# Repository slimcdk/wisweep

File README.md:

Feel free to support me and the development I do!

# WiSweep

Compact WiFi and Bluetooth (5.0) / ZigBee NEMA17 stepper controller featuring stall detection and ultra silent operation. Supply 5-36V upto 3A.

## Production files

## Contribution

Clone repository and fetch submodules

```bash
$ git clone --recursive-submodules git@github.com:slimcdk/wisweep.git
```

## Versioning

Revisions are controlled through git tags such any production easily can be traced back to a commit containing everything. Complete sets of compatible schematics, PCB layouts, documentations, 3D models etc will all stay together under same tag in the source history.

---

## Software uses

* https://www.kicad.org/
* https://www.freecadweb.org/
* https://github.com/features/actions
  * https://github.com/INTI-CMNB/KiBot
* https://code.visualstudio.com/
  * https://marketplace.visualstudio.com/items?itemName=ms-vscode-remote.remote-containers

## Notes

### Parts

`VKMB1001H330MV` can be hard to source - `VKMB1001H220MV` (22µF variant) is an alternative.

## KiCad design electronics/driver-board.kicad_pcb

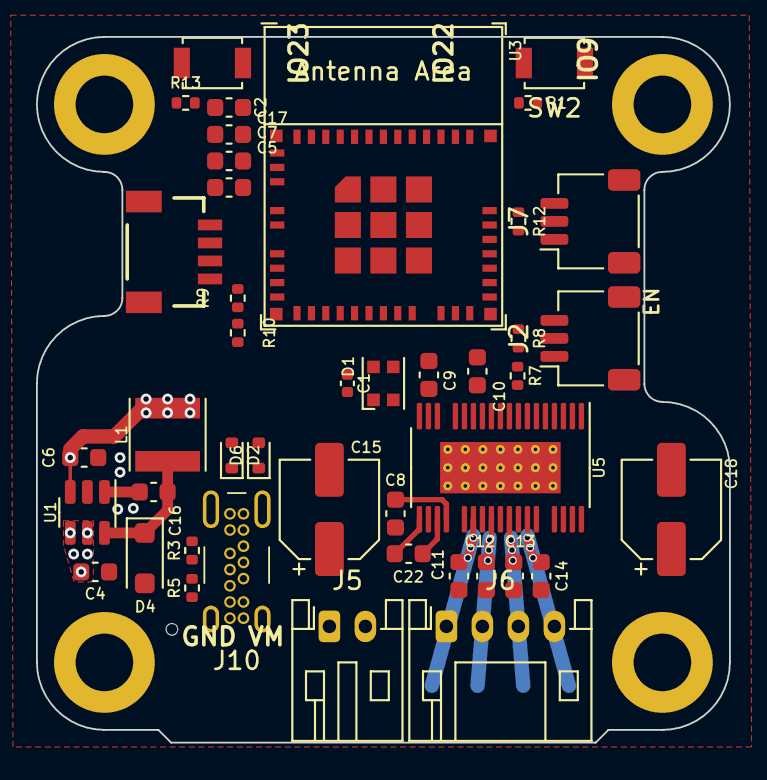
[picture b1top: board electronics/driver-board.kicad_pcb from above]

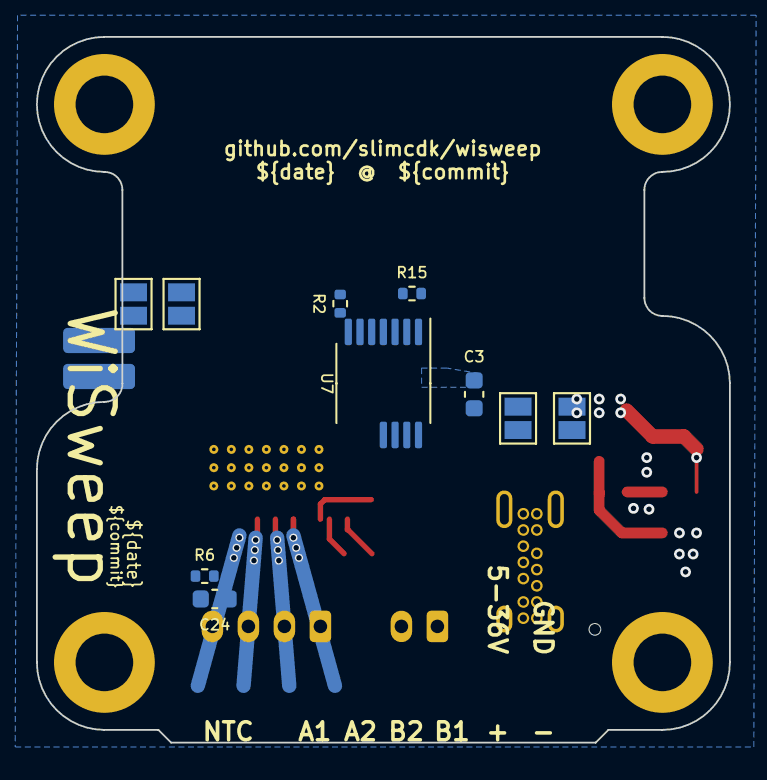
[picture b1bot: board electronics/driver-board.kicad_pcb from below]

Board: 4 copper layers, 38.5 x 39.2 mm, 58 parts (11 on the bottom side), 42 nets.

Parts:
C1: 100nF; C_0402_1005Metric
C2, C7, C8, C13, C14: 1µF; C_0603_1608Metric
C3, C9, C11, C12, C16, C17, C24: 100nF; C_0603_1608Metric
C4, C10: 2.2µF; C_0603_1608Metric
C5, C6: 10µF; C_0603_1608Metric
C15, C18: 33µF; CP_Elec_5x5.9
C22: 22nF; C_0603_1608Metric
D1: WS2812B; LED_WS2812B-2020_PLCC4_2.0x2.0mm
D2, D6: LESD5D5; D_SOD-523
D4: DS210W; D_SOD-123F
H1, H2, H3, H4: M3 MountingHole; MountingHole_3.2mm_M3_DIN965_Pad
J1: Conn_01x02; PinHeader_1x02_P2.00mm_Vertical_SMD_Pin1Left
J2, J7: Conn_01x03; JST_SH_SM03B-SRSS-TB_1x03-1MP_P1.00mm_Horizontal
J4: Qwiic_RA; JST_SMD_1.0mm-4_RA
J5: Conn_01x02; JST_PH_S2B-PH-K_1x02_P2.00mm_Horizontal
J6: Conn_01x04; JST_PH_S4B-PH-K_1x04_P2.00mm_Horizontal
J10: USB_C_Receptacle_USB2.0; USB_C_GT-USB-7036A
JP1, JP2, JP3, JP4: Jumper_2_Open; SolderJumper-2_P1.3mm_Open_Pad1.0x1.5mm
L1: 6.8µH; L_Vishay_IFSC-1515AH_4x4x1.8mm
R1, R2, R6, R8, R9, R10, R12, R13, R15: 10k; R_0402_1005Metric
R3, R5: 5k1; R_0402_1005Metric
R7: 12k; R_0402_1005Metric
SW1, SW2: SW_Push; SW_SPST_B3U-1000P
U1: LMR16006YQ3; SOT-23-6
U3: ESP32-C6-MINI-1/U; ESP32-C6-MINI-1
U5: TMC5240-TSSOP38; TSSOP-38_4.4x9.7mm_P0.5mm
U7: AS5047D; TSSOP-14_4.4x5mm_P0.65mm

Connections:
+3V3: C1.1, C3.2, C5.2, C6.2, C7.2, C9.2, C17.2, D1.1 (VDD), J2.2, J4.2, J7.2, L1.2, R1.2, R2.2, R6.2, R8.2, R9.2, R10.2, R12.2, R13.2, U1.3 (FB), U3.3 (3V3), U5.11 (VCC_IO), U7.11 (VDD), U7.12 (VDD3V3)
+5V: J10.A4 (VBUS), J10.A9 (VBUS), J10.B4 (VBUS), J10.B9 (VBUS)
/AS_ENCA: JP1.1 (A), U5.14 (ENCA), U7.7 (A)
/AS_ENCB: JP2.1 (A), U5.13 (ENCB), U7.6 (B)
/AS_ENCN: U5.12 (ENCN), U7.14 (I/PWM)
/ESP_BOOT: R1.1, SW2.2, U3.23 (GPIO9)
/ESP_EN: C2.1, R13.1, SW1.1, U3.8 (EN/CHIP_PU)
/ESP_GPIO0: R15.1, U3.12 (GPIO0/ADC1_CH0/XTAL_32K_P), U5.15 (DRV_EN)
/ESP_GPIO1: JP1.2 (B), U3.13 (GPIO1/ADC1_CH1/XTAL_32K_N)
/ESP_GPIO2: D1.4 (DIN), U3.5 (GPIO2/ADC1_CH2)
/ESP_GPIO3: JP2.2 (B), U3.6 (GPIO3/ADC1_CH3)
/ESP_GPIO4: U3.9 (MTMS/GPIO4/ADC1_CH4), U5.18 (DIAG1/SW)
/ESP_GPIO5: U3.10 (MTDI/GPIO5/ADC1_CH5), U5.17 (DIAG0)
/ESP_GPIO6: U3.15 (MTCK/GPIO6/ADC1_CH6), U5.2 (SDO/NAO), U7.3 (MISO)
/ESP_GPIO7: R2.1, U3.16 (MTDO/GPIO7), U7.1 (~CS)
/ESP_GPIO8: U3.22 (GPIO8), U5.38 (SCK/AD1), U7.2 (CLK)
/ESP_GPIO12: D2.2 (A2), J10.A7 (D-), J10.B7 (D-), U3.17 (GPIO12/USB_D-)
/ESP_GPIO13: D6.2 (A2), J10.A6 (D+), J10.B6 (D+), U3.18 (GPIO13/USB_D+)
/ESP_GPIO14: U3.19 (GPIO14), U5.1 (SDI/AD0), U7.4 (MOSI)
/ESP_GPIO15: U3.20 (GPIO15), U5.36 (CS/AD2)
/ESP_GPIO16: J4.4, R10.1, U3.31 (U0TXD/GPIO16)
/ESP_GPIO17: J4.3, R9.1, U3.30 (U0RXD/GPIO17)
/ESP_GPIO20: JP4.2 (B), U3.26 (GPIO20)
/ESP_GPIO21: JP3.1 (A), U3.27 (GPIO21)
/TMC_AIN: C24.2, J1.2, R6.1, U5.8 (AIN)
/TMC_OUT1A: J6.4, U5.32 (OUT1A)
/TMC_OUT1B: J6.2, U5.26 (OUT1B)
/TMC_OUT2A: J6.3, U5.30 (OUT2A)
/TMC_OUT2B: J6.1, U5.28 (OUT2B)
/TMC_REFL: J2.3, JP3.2 (B), R8.1, U5.5 (REFL)
/TMC_REFR: J7.3, JP4.1 (A), R12.1, U5.6 (REFR)
/USB_CC1: J10.A5 (CC1), R5.1
/USB_CC2: J10.B5 (CC2), R3.1
GND: C1.2, C2.2, C3.1, C4.1, C5.1, C6.1, C7.1, C9.1, C10.1, C11.2, C12.2, C13.2, C14.2, C15.2, C17.1, C18.2, C24.1, D1.3 (VSS), D2.1 (A1), D4.2 (A), D6.1 (A1), J1.1, J2.1, J4.1, J5.1, J7.1, J10.A1 (GND), J10.A12 (GND), J10.B1 (GND), J10.B12 (GND), R3.2, R5.2, R7.2, R15.2, SW1.2, SW2.1, U1.2 (GND), U3.1 (GND), U3.2 (GND), U3.11 (GND), U3.14 (GND), U3.36 (GND), U3.37 (GND), U3.38 (GND), U3.39 (GND), U3.40 (GND), U3.41 (GND), U3.42 (GND), U3.43 (GND), U3.44 (GND), U3.45 (GND), U3.46 (GND), U3.47 (GND), U3.48 (GND), U3.49 (GND), U3.50 (GND), U3.51 (GND), U3.52 (GND), U3.53 (GND), U5.3 (CLK), U5.10 (AGND), U5.27 (PGND1), U5.31 (PGND2), U5.39 (EP), U7.5 (TST), U7.13 (GND)
unnamed: C16.1, D4.1 (K), L1.1, U1.6 (SW)
unnamed: C16.2, U1.1 (CB)
unnamed: C22.2, U5.20 (CPI)
unnamed: C22.1, U5.22 (CPO)
unnamed: R7.1, U5.7 (IREF)
unnamed: C8.2, U5.23 (VCP)
unnamed: C10.2, U5.9 (VDD1V8)
VM: C4.2, C8.1, C11.1, C12.1, C13.1, C14.1, C15.1, C18.1, J5.2, U1.4 (~SHDN), U1.5 (VIN), U5.25 (VS1), U5.29 (VS2), U5.33 (VS3), U5.35 (SLEEP)

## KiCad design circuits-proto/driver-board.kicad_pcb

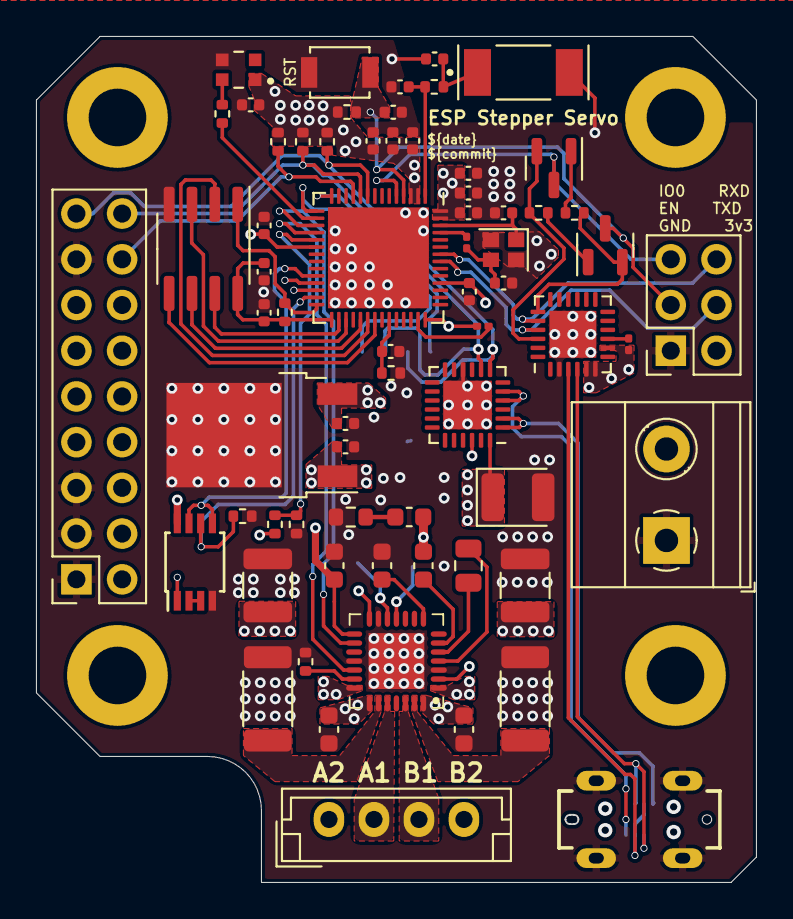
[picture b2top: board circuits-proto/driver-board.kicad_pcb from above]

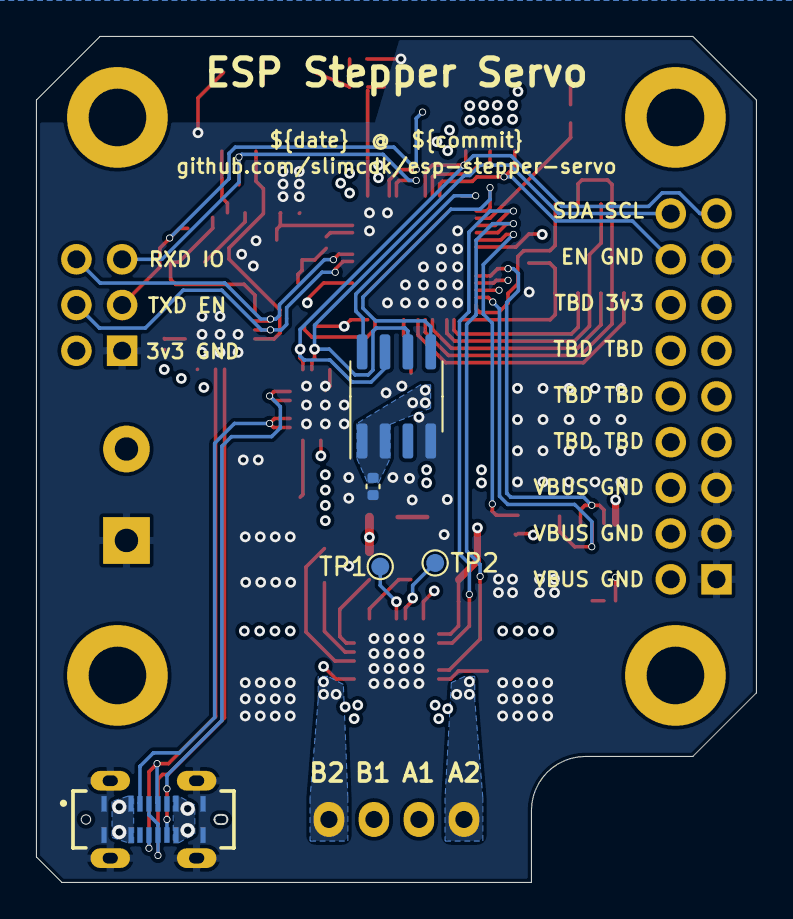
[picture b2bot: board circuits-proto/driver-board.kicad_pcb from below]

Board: 4 copper layers, 40.0 x 47.0 mm, 75 parts (5 on the bottom side), 58 nets.

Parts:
AE1: Antenna; XCVR_NN01-102
C1, C6, C17, C29, C31, C32, C33: 100nF; C_0402_1005Metric
C2, C4, C7, C27, C28, C30: 1µF; C_0402_1005Metric
C3, C5, C25: 10µF; C_0402_1005Metric
C8: 1µF; C_0603_1608Metric
C9: 2.2µF; C_0603_1608Metric
C10, C12, C13, C14: 100nF; C_0603_1608Metric
C11: 22nF; C_0805_2012Metric
C15, C16: 10µF; C_1210_3225Metric
C20: NC; C_0402_1005Metric
C26, C35: 15pF; C_0402_1005Metric
C34: 1pF; C_0402_1005Metric
D1: WS2812B; LED_WS2812C-2020
D3: SMB24A; D_1210_3225Metric
H1, H2, H3, H4: M3 MountingHole; MountingHole_3.2mm_M3_DIN965_Pad
J1: Conn_01x18_Female; PinSocket_2x09_P2.54mm_Vertical
J2: USB4120-03-C_REVA; GCT_USB4120-03-C_REVA
J3: Motor_Conn_01x04; JST_EH_B4B-EH-A_1x04_P2.50mm_Vertical
J4: Screw_Terminals; TerminalBlock_Phoenix_MKDS-1,5-2-5.08_1x02_P5.08mm_Horizont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
J5: Conn_01x06_Female; PinSocket_2x03_P2.54mm_Vertical
L1: 0R; R_0402_1005Metric
L2: 0R; R_0201_0603Metric
Q1, Q2: SS8050-G; SOT-23
R1, R16, R17: 10K; R_0402_1005Metric
R3: 0R100; R_0603_1608Metric
R4: 230R; R_0402_1005Metric
R5: 715K; R_0402_1005Metric
R6: 110K; R_0402_1005Metric
R7, R18: 20K; R_0402_1005Metric
R9, R19: 100K; R_0402_1005Metric
R11: 1K; R_0201_0603Metric
R12, R13: 0R100; R_2010_5025Metric
R14, R20, R21: 4K7; R_0402_1005Metric
R15: 10K; R_0201_0603Metric
SW1: RST_SW_Push; SW_SPST_B3U-1000P
TP1, TP2: TestPoint; TestPoint_Pad_D1.0mm
U1: CP2102N-Axx-xQFN24; QFN-24-1EP_4x4mm_P0.5mm_EP2.6x2.6mm
U2: BA033CC0FP-E2; TO-252-2
U3: ESP32-S3; QFN-56-1EP_7x7mm_P0.4mm_EP5.6x5.6mm
U4: AS5601-ASOT; SOIC-8_3.9x4.9mm_P1.27mm
U5: TMC2209-LA; QFN28P
U6: STUSB4500QTR; QFN-24-1EP_4x4mm_P0.5mm_EP2.7x2.7mm
U7: ESP-PSRAM32; SOIC-8_3.9x4.9mm_P1.27mm
U8: 74LVC2G00; TSSOP-8_3x3mm_P0.65mm
Y1: 40MHz; Crystal_SMD_2016-4Pin_2.0x1.6mm

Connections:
+3V3: C1.1, C4.2, C5.2, C6.2, C7.2, C14.2, C17.2, C25.2, C30.2, C31.2, C32.2, C33.2, D1.1 (VDD), J1.13, J5.2, R1.1, R7.2, R15.1, R20.1, R21.1, U1.5 (VIO), U1.6 (VDD), U1.8 (VBUS), U2.3 (OUT), U3.2 (VDD3P3), U3.3 (VDD3P3), U3.20 (VDD3P3_RTC), U3.46 (VDD3P3_CPU), U3.55 (VDDA), U3.56 (VDDA), U4.1 (VDD5V), U4.2 (VDD3V3), U5.15 (VCC_IO), U6.22 (VSYS), U8.8 (VCC)
/ANTENNA: AE1.1 (A), C34.1, L1.1
/AS5601_A_ITR / ESP_IO09: U3.14 (GPIO9/ADC1_CH8), U4.8 (A)
/AS5601_B_ITR / ESP_IO10: U3.15 (GPIO10/ADC1_CH9), U4.5 (B)
/CP2102_DTR: Q2.2 (E), R16.1, U1.22 (~DSR)
/CP2102_RTS: Q1.2 (E), R17.1, U1.19 (~RTS)
/ESP_EN: C2.1, J5.3, Q1.3 (C), R1.2, SW1.2, U3.4 (CHIP_PU/RESET)
/ESP_IO00: J5.5, Q2.3 (C), U3.5 (GPIO0/BOOT)
/ESP_IO47: C27.2, R14.2, U3.37 (SPICLK_P/GPIO47)
/ESP_SPIVDD: C28.2, C29.2, R9.1, U3.29 (VDD_SPI), U7.8 (VCC)
/I2C_SCL / ESP_IO04: J1.17, R20.2, U3.9 (GPIO4/ADC1_CH3), U4.7 (SCL), U6.7 (SCL)
/I2C_SDA / ESP_IO05: J1.18, R21.2, U3.10 (GPIO5/ADC1_CH4), U4.6 (SDA), U6.8 (SDA)
/LED / ESP_IO11: R4.1, U3.16 (GPIO11/ADC2_CH0)
/SPICLK / ESP_IO30: U3.33 (SPICLK/GPIO30), U7.6 (SCLK)
/SPICS1 / ESP_IO26: R9.2, U3.28 (SPI_CS1/GPIO26), U7.1 (~CE)
/SPID / ESP_IO32: U3.35 (SPID/GPIO32), U7.5 (SI/SIO)
/SPIHD / ESP_IO27: U3.30 (SPIHD/GPIO27), U7.7 (SIO3)
/SPIQ / ESP_IO31: U3.34 (SPIQ/GPIO31), U7.2 (SO/SIO)
/SPIWP / ESP_IO28: U3.31 (SPIWP/GPIO28), U7.3 (SIO2)
/SR_Q / ESP_IO18: U3.24 (GPIO18/ADC2_CH7/DAC_1), U8.5, U8.7
/SR_S / ESP_IO21: R18.1, U3.27 (GPIO21), U8.6
/TMC2209_BRA: R12.2, U5.23 (BRA)
/TMC2209_BRB: R13.2, U5.27 (BRB)
/TMC2209_DIAG: TP1.1, U5.11 (DIAG), U8.1
/TMC2209_DIR / ESP_IO13: U3.18 (GPIO13/ADC2_CH2), U5.19 (DIR)
/TMC2209_EN / ESP_IO06: J1.16, R7.1, U3.11 (GPIO6/ADC1_CH5), U5.2 (ENN)
/TMC2209_IDX: TP2.1, U5.12 (INDEX)
/TMC2209_OA1: J3.2, U5.24 (OA1)
/TMC2209_OA2: J3.1, U5.21 (OA2)
/TMC2209_OB1: J3.3, U5.26 (OB1)
/TMC2209_OB2: J3.4, U5.1 (OB2)
/TMC2209_STEP / ESP_IO12: U3.17 (GPIO12/ADC2_CH1), U5.16 (STEP)
/UART0_RXD / ESP_IO44: J5.6, U1.20 (RXD), U3.50 (U0RXD/PROG/GPIO44)
/UART0_TXD / ESP_IO43: J5.4, U1.21 (TXD), U3.49 (U0TXD/PROG/GPIO43)
/UART1_RXD / ESP_IO46: R11.2, U3.42 (GPIO37), U5.14 (PDN_UART)
/UART1_TXD / ESP_IO45: R11.1, U3.41 (GPIO36)
/USB_CC1: J2.A5 (CC1), U6.1 (CC1DB), U6.2 (CC1)
/USB_CC2: J2.B5 (CC2), U6.4 (CC2), U6.5 (CC2DB)
/USB_D+: J2.A6 (D1+), J2.B6 (D2+), U1.3 (D+)
/USB_D-: J2.A7 (D1-), J2.B7 (D2-), U1.4 (D-)
/VBUS_SENSE / ESP_IO14: R5.2, R6.1, U3.19 (GPIO14/ADC2_CH3)
GND: AE1.2 (Shield), C1.2, C2.2, C3.1, C4.1, C5.1, C6.1, C7.1, C9.2, C12.2, C13.2, C14.1, C15.2, C16.2, C17.1, C20.2, C25.1, C26.1, C27.1, C28.1, C29.1, C30.1, C31.1, C32.1, C33.1, C34.2, C35.1, D1.3 (VSS), D3.2 (A), J1.1, J1.3, J1.5, J1.15, J2.A1 (GND_A), J2.A12 (GND_A), J2.B1 (GND_B), J2.B12 (GND_B), J2.S1 (SHIELD), J2.S2 (SHIELD), J2.S3 (SHIELD), J2.S4 (SHIELD), J4.1, J5.1, R3.2, R6.2, R12.1, R13.1, R14.1, R18.2, R19.2, SW1.1, U1.2 (GND), U1.25 (GND), U2.2 (GND), U3.57 (GND), U4.4 (GND), U5.3 (GND), U5.13 (CLK), U5.18 (GND), U5.29 (PAD), U6.10 (GND), U6.25 (GND), U7.4 (VSS), U8.4 (GND), Y1.2, Y1.4
unnamed: C8.2, R3.1
unnamed: C9.1, U5.8 (5VOUT)
unnamed: C10.2, U5.6 (VCP)
unnamed: C11.1, U5.5 (CPI)
unnamed: C11.2, U5.4 (CPO)
unnamed: C20.1, L1.2, U3.1 (LNA_IN/RF)
unnamed: C26.2, L2.1, Y1.3
unnamed: C35.2, U3.54 (XTAL_P), Y1.1
unnamed: D1.4 (DIN), R4.2
unnamed: L2.2, U3.53 (XTAL_N)
unnamed: Q1.1 (B), R16.2
unnamed: Q2.1 (B), R17.2
unnamed: R15.2, U1.9 (~RST)
unnamed: R19.1, U5.20 (STDBY)
unnamed: U8.2, U8.3
VBUS: C3.2, C8.1, C10.1, C12.1, C13.1, C15.1, C16.1, D3.1 (K), J1.2, J1.4, J1.6, J2.A4 (VBUS_A), J2.A9 (VBUS_A), J2.B4 (VBUS_B), J2.B9 (VBUS_B), J4.2, R5.1, U2.1 (VCC), U5.22 (VS), U5.28 (VS), U6.24 (VDD)

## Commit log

2021-07-07 Initial commit with existing project files
2021-07-07 Fixed references with external KiCAD library
2021-07-15 Added backpack template
2021-07-15 Work on schematics
2022-01-30 working on simplified design
2022-04-17 kicad 6; schematic updates; kicad deps update
2022-04-17 Contribution readme addition
2022-04-17 removed generated kicad files
2022-04-17 updated external library collection
2022-04-17 updated 3d models
2022-04-17 refresh 3d models
2022-04-23 work on external spram and pcb layout
2022-04-25 couple of renders
2022-04-28 unignoring pdfs
2022-04-28 adjusting schematic and pcb component placement
2022-05-21 tmc2209 -> tmc 2226
2022-05-21 added dependabot
2022-05-21 Bump dependencies/slimc-kicad-libraries from `45df5fe` to `776c4c0`
    Bumps [dependencies/slimc-kicad-libraries](https://github.com/slimcdk/slimc-kicad-libraries) from `45df5fe` to `776c4c0`.
    - [Release notes](https://github.com/slimcdk/slimc-kicad-libraries/releases)
    - [Commits](https://github.com/slimcdk/slimc-kicad-libraries/compare/45df5fe23d12ba9b8426a062f9e0f9d578703c0f...776c4c0c124f4bd78e0c5a3a3f7883d8be826b2f)
    ---
    updated-dependencies:
    - dependency-name: dependencies/slimc-kicad-libraries
2022-05-21 Bump actions/upload-artifact from 2 to 3
    Bumps [actions/upload-artifact](https://github.com/actions/upload-artifact) from 2 to 3.
    - [Release notes](https://github.com/actions/upload-artifact/releases)
    - [Commits](https://github.com/actions/upload-artifact/compare/v2...v3)
    ---
    updated-dependencies:
    - dependency-name: actions/upload-artifact
2022-05-21 Bump actions/checkout from 2 to 3
    Bumps [actions/checkout](https://github.com/actions/checkout) from 2 to 3.
    - [Release notes](https://github.com/actions/checkout/releases)
    - [Changelog](https://github.com/actions/checkout/blob/main/CHANGELOG.md)
    - [Commits](https://github.com/actions/checkout/compare/v2...v3)
    ---
    updated-dependencies:
2022-05-22 Bump INTI-CMNB/KiBot from 0.7.0 to 2
    Bumps [INTI-CMNB/KiBot](https://github.com/INTI-CMNB/KiBot) from 0.7.0 to 2.
    - [Release notes](https://github.com/INTI-CMNB/KiBot/releases)
    - [Changelog](https://github.com/INTI-CMNB/KiBot/blob/master/CHANGELOG.md)
    - [Commits](https://github.com/INTI-CMNB/KiBot/compare/v0.7.0...v2)
    ---
    updated-dependencies:
2022-05-24 gha bundling of backpack board
2022-05-24 fixing gha key indent
2022-05-24 kibot schematic and bom
2022-05-24 gha kibot testing
2022-05-24 changed name ref
2022-05-24 changed artifact path
2022-05-24 date marker
2022-05-25 devcontainer with kicad 6
2022-05-25 workflow kibot generate schematics with text replace
2022-05-25 fixing file permissions for gha
2022-05-25 more kibot and exports
2022-05-25 fixed schematic ref
2022-05-25 updated gha
2022-05-25 removed jpg from ignore
2022-05-25 kibot gha path and esphome config validation
2022-05-25 renamed gha
2022-05-25 added esphome firmware config
2022-05-25 workflow generated exports
2022-05-25 removed duplicate url. Removed secrets refs
2022-05-25 fixed schematic ref in readme
2022-05-26 hq renders
2022-05-26 adjusting renders and readmne
2022-05-28 adjusting gha
2022-05-28 latest renders
2022-05-28 change dateformat
2022-05-28 fixing gha
2022-05-28 pcb layout redone
2022-05-28 removed misplaced line
2022-05-28 gha project compiling include esphome
2022-05-28 do not depend on fw validation yet
2022-06-06 adjusted tmc2209 circuitry and redid overall comp placement
2022-06-06 labels on pcb
2022-06-06 kicad config testing
2022-06-06 kicad main config testing
2022-06-07 another round of overall placement
2022-06-10 fixed duplicate usbc connector
2022-06-10 first tracing
2022-06-10 ore tracing
2022-06-12 first finished tracing; missing expboard connections and bom
2022-06-12 updated groundplanes
2022-06-13 kibot pcbway gerbers
2022-06-13 gh action and kibot
2022-06-13 do not convert report to pdf
2022-06-13 changed gpio for step/dir
2022-06-14 production artifacts in own archive
2022-06-14 more workflow testing
2022-06-14 removed firmware and updated kibot
2022-06-14 removed images with git hash
2022-06-14 gha create static dir if not present
2022-06-14 removed firmware archival from gha
2022-06-14 flipped symbol
2022-06-14 moved internal traces to back layer
2022-06-14 exclude connectors from pcba fitting
2022-06-16 added info for BOM; redid some traces and labels
2022-06-18 replaced a few passive components and improved supply/common loop
2022-06-20 schematic changes
2023-05-01 Bump dependencies/slimc-kicad-libraries from `776c4c0` to `f0ecbd1`
    Bumps [dependencies/slimc-kicad-libraries](https://github.com/slimcdk/slimc-kicad-libraries) from `776c4c0` to `f0ecbd1`.
    - [Release notes](https://github.com/slimcdk/slimc-kicad-libraries/releases)
    - [Commits](https://github.com/slimcdk/slimc-kicad-libraries/compare/776c4c0c124f4bd78e0c5a3a3f7883d8be826b2f...f0ecbd151ba71713c37f5e37a63a6f68fea80327)
    ---
    updated-dependencies:
    - dependency-name: dependencies/slimc-kicad-libraries
2023-07-11 persist current design
2023-07-29 current state
2023-07-29 updated library paths
2023-07-29 remove duplicate folder
2023-07-29 some test points
2023-08-07 refactored a little
2023-08-07 work on module prototype
2023-08-07 fixed directory name
2023-11-05 tmc5240/ad5074d/esp32c6 board to be ordered
2023-11-05 fixing stuff
2023-11-05 workflow fixes
2023-11-05 workflow debugging
2023-11-05 all vias have 0.3mm bore
2023-11-05 workflow update
2023-11-05 hiding motor connector
2023-11-05 hiding missing 3d models
2023-11-05 changed thermal vias to 0.3mm bore
2023-11-05 updated vias to 0.25mm bore
2023-11-06 changed some 0402 caps to 0603
2023-11-06 changed motor connector to jst-xh
2023-11-06 extra render
2023-11-06 fixing renders
2023-11-06 fixing angle
2023-11-06 adjusting renders
2023-11-06 more render fixing
2023-11-06 removing some renders
2023-11-06 trying to fix timeout
2023-11-06 adjusting render angle
2023-11-06 filled in part numbers
2023-11-07 work on kibot
2023-11-07 Bump actions/checkout from 3 to 4
    Bumps [actions/checkout](https://github.com/actions/checkout) from 3 to 4.
    - [Release notes](https://github.com/actions/checkout/releases)
    - [Changelog](https://github.com/actions/checkout/blob/main/CHANGELOG.md)
    - [Commits](https://github.com/actions/checkout/compare/v3...v4)
    ---
    updated-dependencies:
2023-11-07 fixed typo
2023-11-07 removed kibot diff and added ibom
2023-11-07 removed empty options
2023-11-07 fixing errors
2023-11-07 kibot all exports
2023-11-07 archive selected files
2023-11-07 fixed render outputs for project
2023-11-07 fixed errors..
2023-11-07 project files and image
2023-11-07 renders without commit hash
2023-11-07 tmc5240 datasheet; generated directory
2023-11-07 testing kicost
2023-11-09 kicost stuff
2023-11-09 added back all generators
2023-11-09 splitted power cap into two and changed connector to wago
2023-11-09 disable mouser api
2023-11-10 fixed tmc5240 fp and esp32 boot pins
2023-11-10 power labels
2023-11-11 connected encoder index
2023-11-14 new board layout; stripped 5v line and added qwiic and some buttons
2023-11-14 moved a few traces to give space for ground path
2023-11-14 pull ups for i2c; teardrops on through hole connections
2023-11-15 unified gerbers build
2023-11-15 fixed few connector part numbers
2023-11-20 new 3v3 power circuitry; renamed project
2023-11-21 moved few tracks and changed track width from 0.2 -> 0.25
2023-11-21 adjusting pnp file generation
2023-11-21 fix spelling
2023-11-21 renaming pnp headers for jlcpcb
2023-11-21 added teardrops
2023-11-29 added LICENSE
2023-11-30 changed rgb led and updated routing/tracks
2023-11-30 updates to traces
2023-11-30 moved more traces around
2023-12-18 Bump actions/upload-artifact from 3 to 4
    Bumps [actions/upload-artifact](https://github.com/actions/upload-artifact) from 3 to 4.
    - [Release notes](https://github.com/actions/upload-artifact/releases)
    - [Commits](https://github.com/actions/upload-artifact/compare/v3...v4)
    ---
    updated-dependencies:
    - dependency-name: actions/upload-artifact
2024-11-25 incorporated USB port and refined board layout wip
2024-11-25 bump gh action to kicad8
2024-11-25 zoom out for renders
2024-11-25 zoom out
2024-11-26 wip 4-layer layout
2024-11-28 clean up
2024-11-28 more routing
2024-11-28 kicad8 devcontainer
2024-11-28 fixed some broken references and kibot jobs
2024-11-28 fixed few render issues
2024-12-01 added ldo for USB
2024-12-01 added few ground vias
2024-12-11 reworked layout a bit
2025-01-04 Update README.md with buy-me-a-coffee
2025-02-15 wip usb jtag and power connectors
2025-02-15 testing new layout
2025-08-12 Bump actions/checkout from 3 to 5
    Bumps [actions/checkout](https://github.com/actions/checkout) from 3 to 5.
    - [Release notes](https://github.com/actions/checkout/releases)
    - [Changelog](https://github.com/actions/checkout/blob/main/CHANGELOG.md)
    - [Commits](https://github.com/actions/checkout/compare/v3...v5)
    ---
    updated-dependencies:
2025-10-27 Bump actions/upload-artifact from 4 to 5
    Bumps [actions/upload-artifact](https://github.com/actions/upload-artifact) from 4 to 5.
    - [Release notes](https://github.com/actions/upload-artifact/releases)
    - [Commits](https://github.com/actions/upload-artifact/compare/v4...v5)
    ---
    updated-dependencies:
    - dependency-name: actions/upload-artifact
2025-11-24 Bump actions/checkout from 3 to 6
    Bumps [actions/checkout](https://github.com/actions/checkout) from 3 to 6.
    - [Release notes](https://github.com/actions/checkout/releases)
    - [Changelog](https://github.com/actions/checkout/blob/main/CHANGELOG.md)
    - [Commits](https://github.com/actions/checkout/compare/v3...v6)
    ---
    updated-dependencies:
2025-12-15 Bump actions/upload-artifact from 4 to 6
    Bumps [actions/upload-artifact](https://github.com/actions/upload-artifact) from 4 to 6.
    - [Release notes](https://github.com/actions/upload-artifact/releases)
    - [Commits](https://github.com/actions/upload-artifact/compare/v4...v6)
    ---
    updated-dependencies:
    - dependency-name: actions/upload-artifact
